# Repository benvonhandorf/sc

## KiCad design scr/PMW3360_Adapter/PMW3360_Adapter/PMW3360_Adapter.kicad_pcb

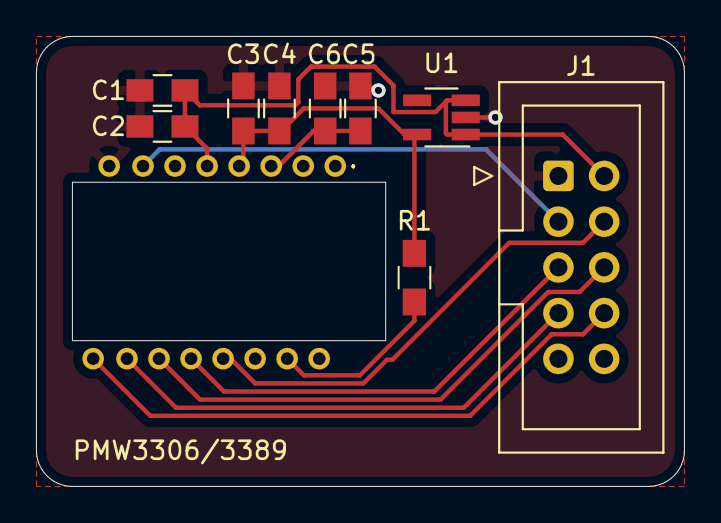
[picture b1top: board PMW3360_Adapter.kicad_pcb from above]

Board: 2 copper layers, 36.0 x 25.0 mm, 10 parts (0 on the bottom side), 11 nets.

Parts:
C1, C4: 10uF; C_0805_HandSoldering
C2, C3, C6: 100nF; C_0805_HandSoldering
C5: 4.7uF; C_0805_HandSoldering
J1: Conn_02x05_Odd_Even; IDC-Header_2x05_P2.54mm_Vertical
R1: 39R; R_0805_HandSoldering
U1: TLV70019_SOT23-5; SOT-23-5_HandSoldering
U2: PMW3360

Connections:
+1V8: C3.1, C4.1, R1.1, U1.5, U2.4
+3V3: C1.1, C2.1, J1.2, U1.1, U1.3, U2.5
GND: C1.2, C2.2, C3.2, C4.2, C5.2, C6.2, J1.1, U1.2, U2.8
MISO: J1.5, U2.12
MOSI: J1.6, U2.11
MOTION: J1.8, U2.9
unnamed: C5.1, C6.1, U2.3
unnamed: R1.2, U2.15
SCLK: J1.7, U2.10
~CS: J1.4, U2.13
~RST: J1.3, U2.7

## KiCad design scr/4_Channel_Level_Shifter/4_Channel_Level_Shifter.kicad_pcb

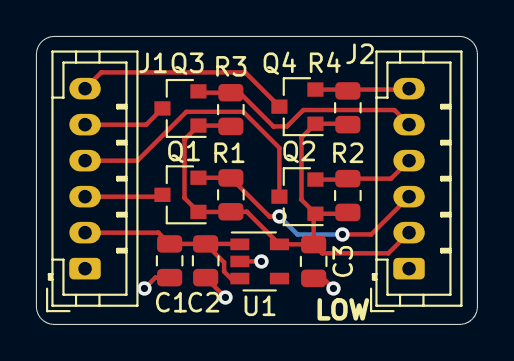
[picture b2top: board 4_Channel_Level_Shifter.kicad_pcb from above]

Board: 2 copper layers, 24.5 x 16.0 mm, 14 parts (0 on the bottom side), 11 nets.

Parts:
C1: 10uF; C_0805_2012Metric
C2, C3: 1uF; C_0805_2012Metric
J1: High Voltage; JST_PH_B6B-PH-K_1x06_P2.00mm_Vertical
J2: Target Voltage; JST_PH_B6B-PH-K_1x06_P2.00mm_Vertical
Q1, Q2, Q3, Q4: 2N7002; SOT-23
R1, R2, R3, R4: 1k; R_0805_2012Metric
U1: TLV70018_SOT23-5; SOT-23-5

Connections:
1_H: J1.3, Q1.3
1_L: J2.3, Q1.2, R1.2
2_H: J1.4, Q2.3
2_L: J2.4, Q2.2, R2.2
3_H: J1.5, Q3.3
3_L: J2.5, Q3.2, R3.2
4_H: J1.6, Q4.3
4_L: J2.6, Q4.2, R4.2
GND: C1.2, C2.2, C3.2, J1.1, J2.1, U1.2
VCC: C1.1, C2.1, J1.2, U1.1, U1.3
VDD: C3.1, J2.2, Q1.1, Q2.1, Q3.1, Q4.1, R1.1, R2.1, R3.1, R4.1, U1.5

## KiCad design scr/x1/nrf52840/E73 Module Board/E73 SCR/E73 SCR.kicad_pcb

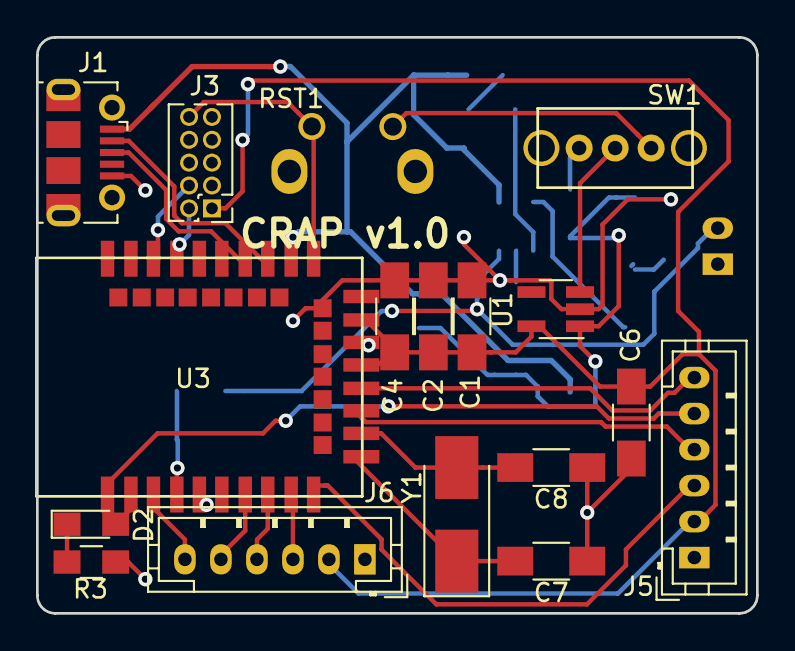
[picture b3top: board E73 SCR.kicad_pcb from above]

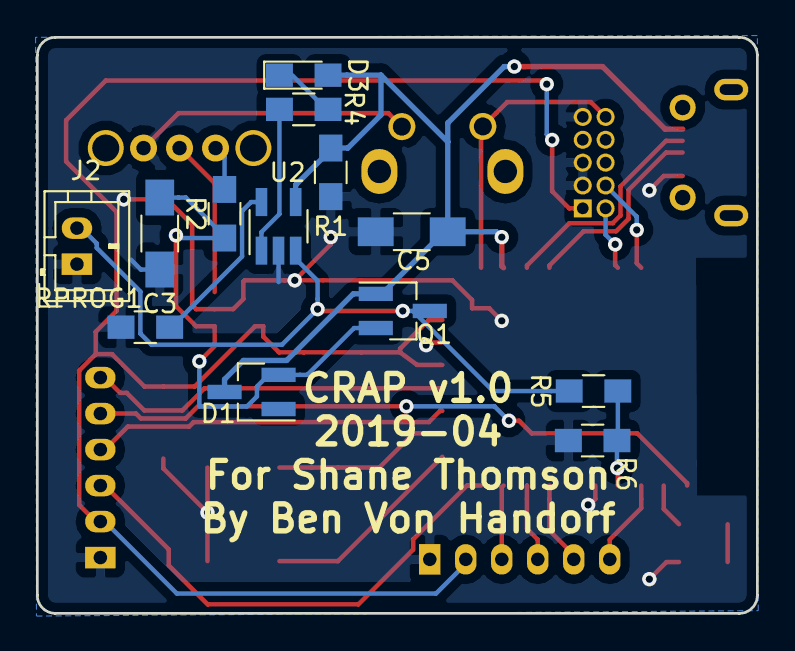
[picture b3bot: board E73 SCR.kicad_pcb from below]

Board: 2 copper layers, 40.0 x 32.0 mm, 30 parts (13 on the bottom side), 28 nets.

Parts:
C1, C3, C5, C6: 10uF; C_1206_HandSoldering
C2, C4: 0.1uF; C_1206_HandSoldering
C7, C8: 22pF; C_1206_HandSoldering
D1: BAT54S; SOT-23_Handsoldering
D2: LED; LED_0805_HandSoldering
D3: CHG; LED_0805_HandSoldering
J1: USB_B_Micro; USB_Micro-B_Molex-105017-0001
J2: BAT; JST_PH_B2B-PH-K_02x2.00mm_Straight
J3: SWD; Pin_Header_Straight_2x05_Pitch1.27mm
J5: SWTCH; JST_PH_B6B-PH-K_06x2.00mm_Straight
J6: JOY; JST_PH_B6B-PH-K_06x2.00mm_Straight
Q1: AO3401; SOT-23_Handsoldering
R1, R2, R5, R6: 100K; R_0805_HandSoldering
R3, R4: 1K; R_0805_HandSoldering
RPROG1: 4.7K; R_0805_HandSoldering
RST1: SW_SPST; Tac_SPST_RightAngle_SideActuated_THT
SW1: SW_BAT; OS102011MA1QN1
U1: AP2112K-3.3; SOT-23-5_HandSoldering
U2: MCP73831-2-OT; SOT-23-5_HandSoldering
U3: E73-2G4M08S1C-52840; E73(2G4M08S1C)-HandSoldered
Y1: 32,767 Hz; Crystal_SMD_5032-2pin_5.0x3.2mm_HandSoldering

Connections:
+3V3: C1.1, C2.1, C4.1, C6.1, J3.1, J5.2, J6.2, U1.5, U3.19, U3.23
+BATT: J2.2, Q1.3, R5.1, U2.3
A1_P003: J6.6, U3.3
BATSENSE: R5.2, R6.1, U3.4
D+: J1.3, U3.31
D-: J1.2, U3.29
GND: C1.2, C2.2, C3.2, C4.2, C5.2, C6.2, C7.1, C8.1, J1.5, J2.1, J3.3, J3.5, J3.9, J5.1, J6.1, R1.2, R3.1, R6.2, RPROG1.2, RST1.1, SW1.1, U1.2, U2.2, U3.5, U3.21, U3.24
LCLK: J5.3, U3.10
LED: D2.2, U3.2
unnamed: C3.1, D1.2, Q1.2, R2.1, U1.1
unnamed: D2.1, R3.2
unnamed: D3.1, R4.1
unnamed: R2.2, SW1.3
unnamed: R4.2, U2.1
unnamed: RPROG1.1, U2.5
unnamed: SW1.2, U1.3
P1_09: J5.6, U3.17
P1_11: J5.5, U3.1
RCLK: J5.4, U3.15
RESET: J3.10, RST1.2, U3.26
SW: J6.5, U3.7
SWCLK: J3.4, U3.39
SWDIO: J3.2, U3.37
VBUS: C5.1, D1.3, D3.2, J1.1, Q1.1, R1.1, U2.4, U3.27
X: J6.3, U3.9
XL1: C7.2, U3.11, Y1.1
XL2: C8.2, U3.13, Y1.2
Y: J6.4, U3.8

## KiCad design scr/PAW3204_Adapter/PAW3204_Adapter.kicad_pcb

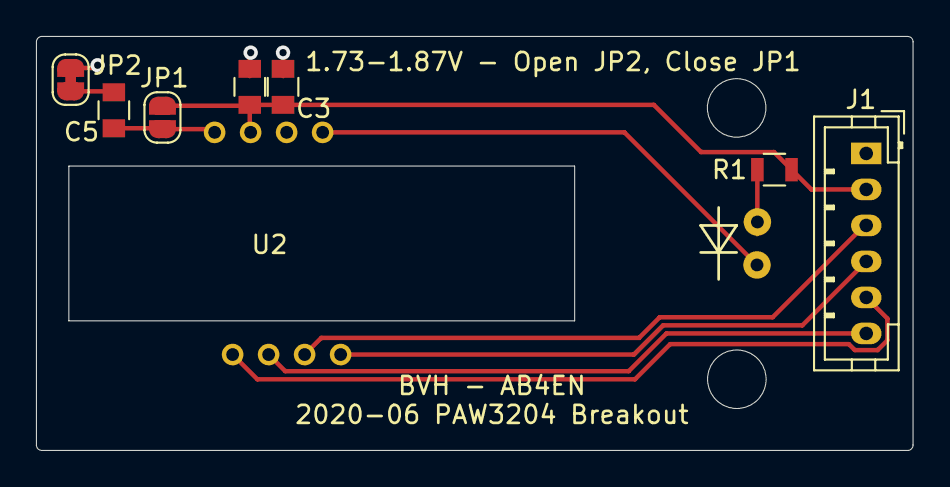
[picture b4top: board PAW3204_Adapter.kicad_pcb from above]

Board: 2 copper layers, 48.7 x 23.0 mm, 8 parts (0 on the bottom side), 10 nets.

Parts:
C3: 10uF; C_0805
C4: 0.1uF; C_0805
C5: 1uF; C_0805
J1: Conn_01x06; JST_PH_B6B-PH-K_06x2.00mm_Straight
JP1: VDDA_VDD; SolderJumper-2_P1.3mm_Open_RoundedPad1.0x1.5mm
JP2: VDDA_GND; SolderJumper-2_P1.3mm_Bridged_RoundedPad1.0x1.5mm
R1: R; R_0805
U2: PAW3204

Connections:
GND: C3.2, C4.2, J1.1, JP2.2, U2.6
LED_A: R1.2, U2.9
LED_C: U2.5, U2.10
MOTSWK: J1.6, U2.2
unnamed: C5.2, JP2.1
RST: J1.5, U2.1
SCLK: J1.4, U2.4
SDIO: J1.3, U2.3
VDD: C3.1, C4.1, J1.2, JP1.2, R1.1, U2.7
VDDA: C5.1, JP1.1, U2.8

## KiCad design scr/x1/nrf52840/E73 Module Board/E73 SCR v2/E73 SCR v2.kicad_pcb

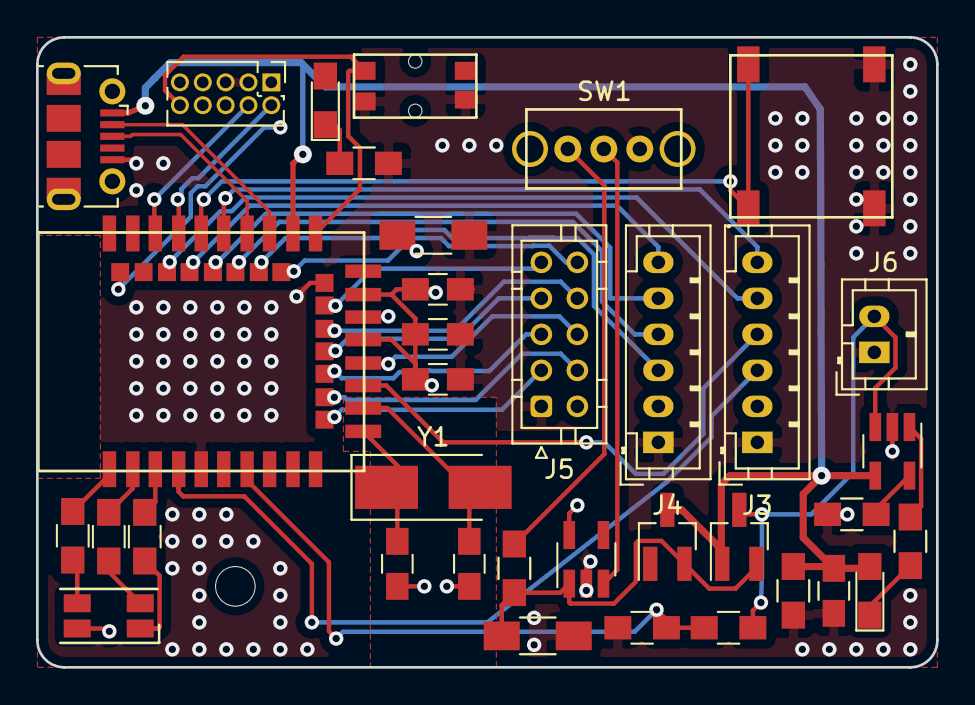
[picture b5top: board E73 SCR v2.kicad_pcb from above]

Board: 4 copper layers, 50.0 x 35.0 mm, 36 parts (0 on the bottom side), 43 nets.

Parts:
C1, C4: 10uF; C_0805_HandSoldering
C2, C3: 0.1uF; C_0805_HandSoldering
C5, C6: 22pF; C_0805_HandSoldering
C7, C8: 10uF; C_1206_HandSoldering
D1: LED_RGBA; LED_RGB_1210
D2: LED; LED_0805_HandSoldering
D3: BAT54S; SOT-23_Handsoldering
D4: CHG; LED_0805_HandSoldering
J1: SWD; Pin_Header_Straight_2x05_Pitch1.27mm
J2: USB_B_Micro; USB_Micro-B_Molex-105017-0001
J3: XC1; JST_PH_B6B-PH-K_06x2.00mm_Straight
J4: XC2; JST_PH_B6B-PH-K_06x2.00mm_Straight
J5: XC3; JST_PHD_B10B-PHDSS_2x05_P2.00mm_Vertical
J6: BAT; JST_PH_B2B-PH-K_02x2.00mm_Straight
LS1: Speaker; SMD_Speaker
Q1: AO3401; SOT-23_Handsoldering
R1, R2, R3, R4, R7: 1K; R_0805_HandSoldering
R5, R6, R8, R9: 100K; R_0805_HandSoldering
RPROG1: 4.7K; R_0805_HandSoldering
RST1: SW_SPST; Tac_SMD_6.4mm_Side_SPST_NO
SW1: SW_BAT; OS102011MA1QN1
U1: E73-2G4M08S1C-52840; E73(2G4M08S1C)-HandSoldered
U2: MCP73831-2-OT; SOT-23-5_HandSoldering
U3: AP2112K-3.3; SOT-23-5_HandSoldering
Y1: 32,767 Hz; Crystal_SMD_5032-2pin_5.0x3.2mm_HandSoldering

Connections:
+3V3: C1.1, C2.1, C3.1, C8.1, D1.4, J1.1, J3.2, J4.2, J5.2, U1.19, U1.23, U3.5
+BATT: J6.2, Q1.3, R5.1, U2.3
BATSENSE: R5.2, R6.1, U1.7
D+: J2.3, U1.31
D-: J2.2, U1.29
GND: C1.2, C2.2, C3.2, C4.2, C5.1, C6.1, C7.2, C8.2, J1.3, J1.5, J1.9, J2.5, J3.1, J4.1, J5.1, J6.1, LS1.2, R4.1, R6.2, R8.2, RPROG1.2, RST1.1, SW1.1, U1.5, U1.21, U1.24, U2.2, U3.2
LED_1: D2.2, U1.42
LED_B: R3.2, U1.1
LED_G: R2.2, U1.2
LED_R: R1.2, U1.3
unnamed: C7.1, D3.2, Q1.2, R9.1, U3.1
unnamed: D1.1, R1.1
unnamed: D1.2, R2.1
unnamed: D1.3, R3.1
unnamed: D2.1, R4.2
unnamed: D4.1, R7.1
unnamed: R7.2, U2.1
unnamed: R9.2, SW1.3
unnamed: RPROG1.1, U2.5
unnamed: SW1.2, U3.3
P0.05_A3: J3.4, U1.15
P0.06: J5.4, U1.14
P0.07: J5.9, U1.22
P0.08: J5.5, U1.16
P0.12: J5.8, U1.20
P0.13: J3.6, U1.33
P0.15: J5.10, U1.28
P0.17: J4.3, U1.30
P0.20: J4.4, U1.32
P0.22: J4.5, U1.34
P0.26: J5.3, U1.12
P0.28_A4: J3.3, U1.4
P1.00: J4.6, U1.36
P1.02: J3.5, U1.38
P1.09: J5.6, U1.17
P.04_A2: J5.7, U1.18
RESET: J1.10, RST1.2, U1.26
SPKR: LS1.1, U1.35
SWCLK: J1.4, U1.39
SWDIO: J1.2, U1.37
VBUS: C4.1, D3.3, D4.2, J2.1, Q1.1, R8.1, U1.27, U2.4
XL1: C5.2, U1.11, Y1.1
XL2: C6.2, U1.13, Y1.2

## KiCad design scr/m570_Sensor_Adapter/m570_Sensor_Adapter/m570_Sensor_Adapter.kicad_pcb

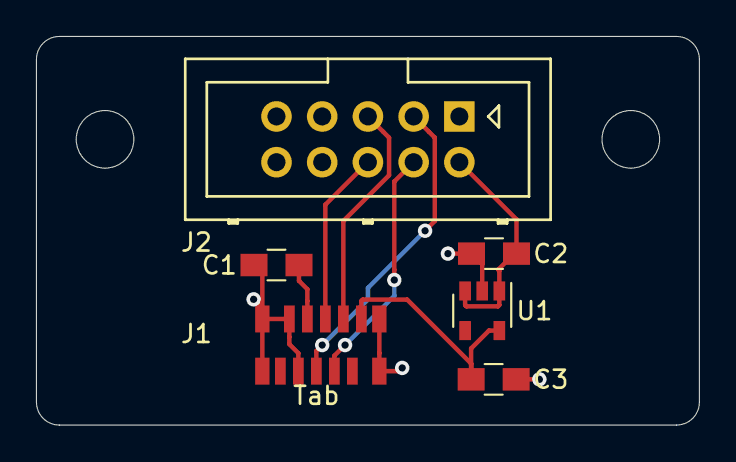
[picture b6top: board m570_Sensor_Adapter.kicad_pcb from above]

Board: 2 copper layers, 36.8 x 21.6 mm, 6 parts (0 on the bottom side), 8 nets.

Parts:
C1, C2, C3: 0.1uF; C_0805_HandSoldering
J1: WM10984CT; Molex_WM10984CT-ND
J2: Conn_02x05_Odd_Even; Multicomp_MC9A12-1034_2x05x2.54mm_Straight
U1: TLV70022_SOT23-5; SOT-23-5

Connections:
+3V3: C2.1, J2.2, U1.1, U1.3
GND: C1.2, C2.2, C3.2, J1.8, J1.9, J1.11, J2.1, U1.2
MISO: J1.3, J2.5
MOSI: J1.4, J2.4
unnamed: C1.1, J1.7
SCK: J1.5, J2.6
VDD: C3.1, J1.1, U1.5
~SS: J1.6, J2.3

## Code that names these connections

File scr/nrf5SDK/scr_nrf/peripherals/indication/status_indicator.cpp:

#include "boards.h"
#include <nrfx_pwm.h>
#include "status_indicator.h"

static nrfx_pwm_t pwmR = NRFX_PWM_INSTANCE(0);
static nrfx_pwm_t pwmG = NRFX_PWM_INSTANCE(1);
static nrfx_pwm_t pwmB = NRFX_PWM_INSTANCE(2);
static nrfx_pwm_t pwmSPKR = NRFX_PWM_INSTANCE(3);

#define FADE_STEP_COUNT 20

static nrf_pwm_values_common_t fade_values[2 * FADE_STEP_COUNT];
static nrf_pwm_sequence_t fade_sequence;

#define CLIP_STEP_COUNT 1024

static nrf_pwm_values_common_t upward_clip_values[CLIP_STEP_COUNT];
static nrf_pwm_sequence_t upward_clip_sequence;

static nrf_pwm_values_common_t downward_clip_values[CLIP_STEP_COUNT];
static nrf_pwm_sequence_t downward_clip_sequence;


static nrf_pwm_values_common_t up_clip_values[1] = {127};
static nrf_pwm_sequence_t up_clip_sequence;

StatusIndicator::StatusIndicator() {
}

void StatusIndicator::initialize() {
  uint16_t value = 0;
  uint16_t step  = NRFX_PWM_DEFAULT_CONFIG_TOP_VALUE / FADE_STEP_COUNT;
  uint16_t  i;
  for (i = 0; i < FADE_STEP_COUNT; ++i)
  {
    value                       += step;
    fade_values[i]              = value;
    fade_values[FADE_STEP_COUNT + i] = NRFX_PWM_DEFAULT_CONFIG_TOP_VALUE - value;
  }

  for (i = 0; i < 256; ++i)
  {
    upward_clip_values[i]              = (i % 6) < 3 ? 255 : 0;
    downward_clip_values[1023 - i]     = (i % 6) < 3 ? 255 : 0;
  }

  for (i = 256; i < 512; ++i)
  {
    upward_clip_values[i]              = (i % 4) < 2 ? 255 : 0;
    downward_clip_values[1023 - i]     = (i % 4) < 2 ? 255 : 0;
  }

  for (i = 512; i < 768; ++i)
  {
    upward_clip_values[i]              = (i % 2) ? 255 : 0;
    downward_clip_values[1023 - i]     = (i % 2) ? 255 : 0;
  }

  for (i = 768; i < CLIP_STEP_COUNT; ++i)
  {
    upward_clip_values[i]              =  127;
    downward_clip_values[1023 - i]     =  127;
  }

  static nrf_pwm_values_t fade_definition = {
    .p_common = fade_values
  };

  fade_sequence.values = fade_definition;
  fade_sequence.length = 2 * FADE_STEP_COUNT;
  fade_sequence.end_delay = 100;

  nrfx_pwm_config_t pwmRConfig = NRFX_PWM_DEFAULT_CONFIG;
  pwmRConfig.output_pins[0] = LED_R | NRFX_PWM_PIN_INVERTED;
  nrfx_pwm_init(&pwmR, &pwmRConfig, NULL);

  nrfx_pwm_config_t pwmGConfig = NRFX_PWM_DEFAULT_CONFIG;
  pwmGConfig.output_pins[0] = LED_G | NRFX_PWM_PIN_INVERTED;
  nrfx_pwm_init(&pwmG, &pwmGConfig, NULL);

  nrfx_pwm_config_t pwmBConfig = NRFX_PWM_DEFAULT_CONFIG;
  pwmBConfig.output_pins[0] = LED_B | NRFX_PWM_PIN_INVERTED;
  nrfx_pwm_init(&pwmB, &pwmBConfig, NULL);

  nrfx_pwm_config_t pwmSPKRConfig = NRFX_PWM_DEFAULT_CONFIG;
  pwmSPKRConfig.output_pins[0] = SPEAKER;
  pwmSPKRConfig.top_value = 255;
  pwmSPKRConfig.base_clock = NRF_PWM_CLK_500kHz;
  nrfx_pwm_init(&pwmSPKR, &pwmSPKRConfig, NULL);

  static nrf_pwm_values_t upward_clip_definition = {
    .p_common = upward_clip_values
  };

  upward_clip_sequence.values = upward_clip_definition;
  upward_clip_sequence.length = CLIP_STEP_COUNT;
  upward_clip_sequence.end_delay = 0;

  static nrf_pwm_values_t up_clip_definition = {
    .p_common = up_clip_values
  };

  up_clip_sequence.values = up_clip_definition;
  up_clip_sequence.length = 1;
  up_clip_sequence.end_delay = 0;

  static nrf_pwm_values_t downward_clip_definition = {
    .p_common = downward_clip_values
  };

  downward_clip_sequence.values = downward_clip_definition;
  downward_clip_sequence.length = CLIP_STEP_COUNT;
  downward_clip_sequence.end_delay = 0;

  initializationStarted();
}

void StatusIndicator::latchSet() {
  latch_set = true;
  nrfx_pwm_simple_playback(&pwmR, &fade_sequence, 1, NRFX_PWM_FLAG_LOOP );
  nrfx_pwm_complex_playback(&pwmSPKR, &upward_clip_sequence, &up_clip_sequence, 1, NRFX_PWM_FLAG_LOOP);
}

void StatusIndicator::latchCleared() {
  if(latch_set) {
    latch_set = false;

    nrfx_pwm_stop(&pwmR, false);
    nrfx_pwm_simple_playback(&pwmSPKR, &downward_clip_sequence, 1, NRFX_PWM_FLAG_STOP);
  }
}

void StatusIndicator::advertisingStarted() {
  nrfx_pwm_simple_playback(&pwmG, &fade_sequence, 1, NRFX_PWM_FLAG_LOOP );
}

void StatusIndicator::bindingComplete() {
  nrfx_pwm_stop(&pwmG, false);
}

void StatusIndicator::initializationStarted() {
  nrfx_pwm_simple_playback(&pwmB, &fade_sequence, 1, NRFX_PWM_FLAG_LOOP );
}

void StatusIndicator::initializationComplete() {
  nrfx_pwm_stop(&pwmB, false);
}

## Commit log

2018-12-23 Clone HID example
2018-12-25 IO Interrupts and ADCs working - Y axis misconfigured
2018-12-25 Switch Y to ADC1, add basic mouse scaling/etc
2018-12-25 Added button handling
2019-02-10 Before HID table rewrite
2019-02-10 Simple mouse will pair
2019-03-17 nrf52840 prototype
2019-03-25 Work to improve dead area
2019-04-07 Add latching for buttons. Refactor to per button and axis data
2019-04-07 Refactor axis and button logic to be independent per input Add neopixel status indication Add latching
2019-04-17 Started work on E73 nrf52840 board
2019-04-19 First PCB routing attempt - Before removing EXT connector
2019-04-30 PCB v1.0
2019-05-12 Script update for CRAP v1 board
2019-05-15 Footprint updated. Total mess
2020-04-18 WIP on E73 board bring up. Requires new variant of board file not using LCXO
2020-04-19 WIP on SPI Trackball implementation
2020-04-19 SPI trackball interface operational
2020-05-21 Initial work on v2 E73 board
2020-05-21 WIP PWM3360 Adapter
2020-05-23 WIP v2
2020-05-25 Initial project structure for nrf sdk application
2020-05-27 Finally have a compiling solution with SPIM enabled.
2020-05-30 Auto stash before merge of "footprint_update" and "origin/footprint_update"
2020-05-30 Basic sigrok protocol decoder
2020-05-30 WIP SPI Debugging
2020-05-30 Debugging
2020-05-30 WIP on bugfixes for SPITrackball
2020-05-31 GPIO work and adding more pins to v2 board
2020-05-31 Library cleanup
2020-05-31 Layout WIP - Floor planning and copper pours
2020-05-31 Fix SS bug
2020-05-31 Basic pointer movement functioning
2020-06-02 Routing and layout almost complete
2020-06-02 v2 fully routed and ready for submission
2020-06-02 PMW3360 Breakout ordered
2020-06-07 Remove protocol analyzer
2020-06-24 PAW3204 adapter and level shifter board
2020-06-24 Added high side PU resistor comment
2020-06-24 WIP button handling
2020-07-08 Button and battery work
2020-07-08 Allow erasing bonds to clear up bad security info
2020-07-18 Battery reporting
2020-07-19 Support for SCR v2 board-Untested
2020-07-23 Latching button support
2020-08-22 BLE device working on v2 hardware
2020-08-23 RGB LED indication working
2020-08-23 Basic speaker feedback
2020-09-07 SPI trackball working before refactor
2020-09-07 Pimoroni trackball working as pointer
2020-09-10 Fix stupid bug around button dirty detection
2020-09-11 Trackball reading scaling
2020-09-20 Acceleration WIP
2023-06-25 Converting to PlatformIO
